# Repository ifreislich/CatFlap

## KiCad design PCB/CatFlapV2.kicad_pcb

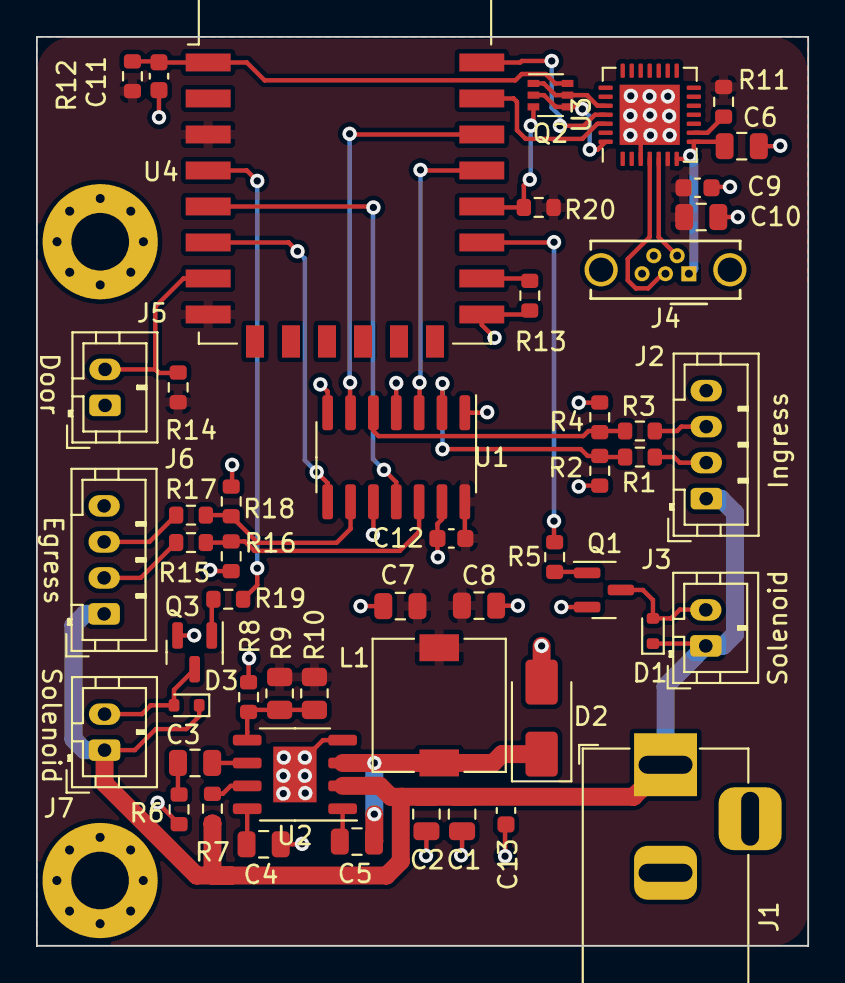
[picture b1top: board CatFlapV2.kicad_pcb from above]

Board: 2 copper layers, 42.8 x 50.5 mm, 53 parts (0 on the bottom side), 40 nets.

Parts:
C1, C2, C10: 10uF; C_0805_2012Metric
C3: 8.2nF; C_0805_2012Metric
C4: 0.47uF; C_0805_2012Metric
C5: 10nf; C_0805_2012Metric
C6: 1uF; C_0805_2012Metric
C7, C8: 22uF; C_0805_2012Metric
C9, C12, C13: 0.1uF; C_0603_1608Metric
C11: 1uF; C_0603_1608Metric
D1, D3: 1N4148W; D_SOD-523
D2: B140-E3; D_SMA
H1, H2: MountingHole; MountingHole_3.2mm_M3_Pad_Via
J1: Barrel_Jack_Switch; BarrelJack_Horizontal
J2: Ingress; JST_PH_B4B-PH-K_1x04_P2.00mm_Vertical
J3, J7: Solenoid; JST_PH_B2B-PH-K_1x02_P2.00mm_Vertical
J4: USB_B_Micro; USB_Micro-B_Wuerth_614105150721_Vertical_CircularHoles
J5: Door; JST_PH_B2B-PH-K_1x02_P2.00mm_Vertical
J6: Egress; JST_PH_B4B-PH-K_1x04_P2.00mm_Vertical
L1: 10uH; L_7.3x7.3_H3.5
Q1, Q3: AO3400; SOT-23
Q2: UMH3N; SOT-363_SC-70-6
R1, R3, R5, R15, R17, R19: 1k; R_0603_1608Metric
R2, R4, R8, R11, R12, R16, R18, R20: 10k; R_0603_1608Metric
R6: 4k02; R_0603_1608Metric
R7: 100k; R_0603_1608Metric
R9: 30k1; R_0805_2012Metric
R10: 180k; R_0805_2012Metric
R13, R14: 1K; R_0603_1608Metric
U1: 74LS125; SOIC-14_3.9x8.7mm_P1.27mm
U2: MP2307DN-LF-Z; HSOP-8-1EP_3.9x4.9mm_P1.27mm_EP2.41x3.1mm
U3: CP2102N-A01-GQFN28; QFN-28-1EP_5x5mm_P0.5mm_EP3.35x3.35mm
U4: ESP-12E

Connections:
+3V3: C7.1, C8.1, C9.1, C10.1, C12.1, L1.2, R9.1, R10.1, R11.2, R12.2, R14.1, R20.2, U1.14 (VCC), U3.6 (VDD), U4.3 (EN), U4.8 (VCC)
+12V: C1.1, C2.1, C13.1, D1.1 (K), D3.1 (K), J1.1, J2.1, J3.1, J6.1, J7.1, R7.2, U2.2 (IN)
/DATA0_0: U1.6, U4.20 (GPIO5)
/DATA0_1: U1.8, U4.6 (GPIO12)
/DATA1_0: U1.3, U4.19 (GPIO4)
/DATA1_1: U1.11, U4.5 (GPIO14)
/DOOR_LATCH1: R5.2, U4.17 (GPIO2)
/DOOR_LATCH2: R19.2, U4.4 (GPIO16)
/DTR: Q2.2 (B1), Q2.4 (E2), U3.28 (~DTR)
/GPIO0: Q2.3 (C2), R20.1, U4.18 (GPIO0)
/RESET: C11.1, Q2.6 (C1), R12.1, U4.1 (~RST)
/RTS: Q2.1 (E1), Q2.5 (B2), U3.24 (~RTS)
/RXD: U3.26 (TXD), U4.21 (GPIO3/RXD)
/TXD: U3.25 (RXD), U4.22 (GPIO1/TXD)
GND: C1.2, C2.2, C4.2, C6.2, C7.2, C8.2, C9.2, C10.2, C11.2, C12.2, C13.2, D2.2 (A), H1.1, H2.1, J1.2, J1.3, J2.4, J4.5 (GND), J4.6 (Shield), J5.1, J6.4, Q1.2 (S), Q3.2 (S), R2.2, R4.2, R6.2, R8.1, R13.2, R16.2, R18.2, U1.1, U1.4, U1.7 (GND), U1.10, U1.13, U2.4 (GND), U2.9 (EP), U3.3 (GND), U3.29 (GND), U4.15 (GND)
unnamed: C3.2, R6.1
unnamed: D1.2 (A), J3.2, Q1.3 (D)
unnamed: C5.2, D2.1 (K), L1.1, U2.3 (SW)
unnamed: D3.2 (A), J7.2, Q3.3 (D)
unnamed: J2.2, R1.1
unnamed: J2.3, R3.1
unnamed: J4.3 (D+), U3.4 (D+)
unnamed: J4.2 (D-), U3.5 (D-)
unnamed: C6.1, J4.1 (VBUS), U3.7 (VREGIN), U3.8 (VBUS)
unnamed: J5.2, R14.2, U4.7 (GPIO13)
unnamed: J6.2, R15.1
unnamed: J6.3, R17.1
unnamed: Q1.1 (G), R5.1
unnamed: Q3.1 (G), R19.1
unnamed: R1.2, R2.1, U1.2
unnamed: R3.2, R4.1, U1.5
unnamed: R15.2, R16.1, U1.12
unnamed: R17.2, R18.1, U1.9
unnamed: C5.1, U2.1 (BS)
unnamed: C3.1, U2.6 (COMP)
unnamed: R7.1, U2.7 (EN)
unnamed: R8.2, R9.2, R10.2, U2.5 (FB)
unnamed: C4.1, U2.8 (SS)
unnamed: R11.1, U3.9 (~RST)
unnamed: R13.1, U4.16 (GPIO15)

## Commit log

2023-11-20 Initial import
2023-11-20 Import PCB design
2023-11-20 Remove leaked SSID Fix table formatting. Refresh the home page every minute.
2024-11-28 Add an optional ntfy.sh topic for each cat. reduce the door swing timeout from 5 to 3 seconds.
2025-12-08 Fix the MDNS responder which needs to be started only once an IP address has been obtained. Correct string lengths and ensure string terminations from for all input data. Reduce dynamic allocations i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
2026-06-29 Move from intellisense to clangd
2026-06-29 Ignore compile_commands.json
